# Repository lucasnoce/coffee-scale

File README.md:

# coffee-scale
Weight measuring device, targeted for coffee making

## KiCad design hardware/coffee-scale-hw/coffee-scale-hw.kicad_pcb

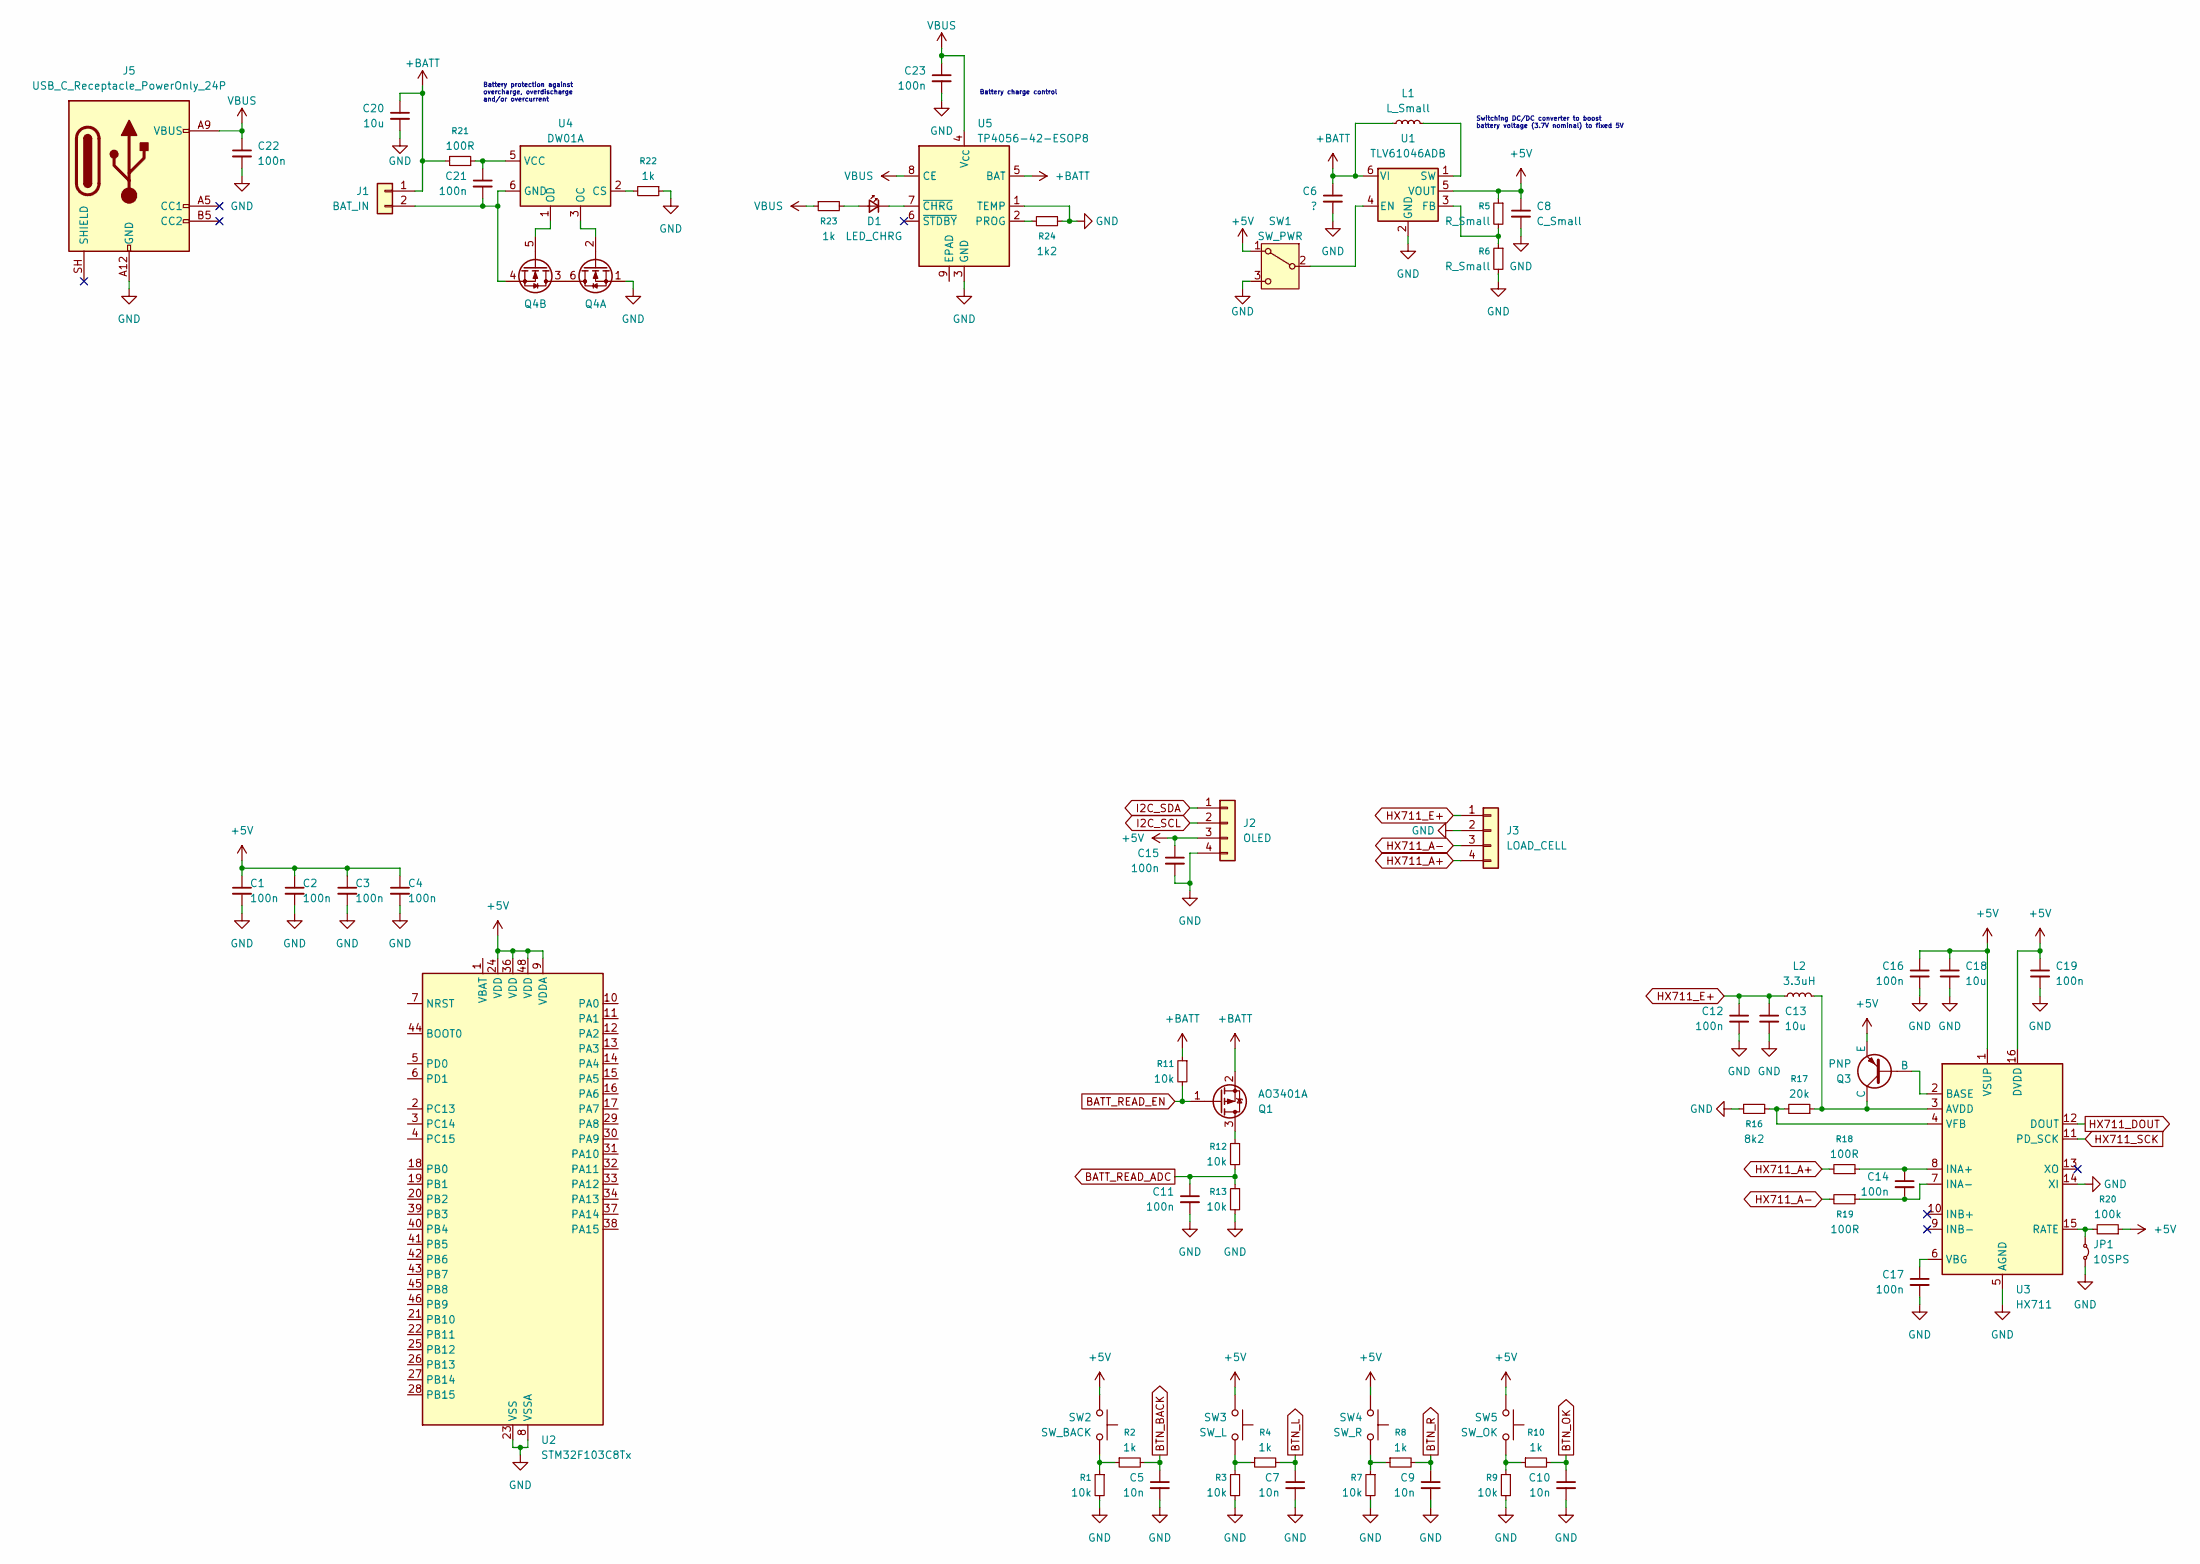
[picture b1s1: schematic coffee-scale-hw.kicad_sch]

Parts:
C1, C2, C3, C4, C11, C12, C14, C15, C16, C17, C19, C21, C22, C23: 100n; C_0805_2012Metric
C5, C7, C9, C10: 10n; C_0805_2012Metric
C6: ?; C_0805_2012Metric
C8: C_Small; C_0805_2012Metric
C13, C18, C20: 10u; C_0805_2012Metric
D1: LED_CHRG; LED_0805_2012Metric
J1: BAT_IN; Terminal_Pad_01x02-3x5mm
J2: OLED; Terminal_Pad_01x04-2x3mm
J3: LOAD_CELL; Terminal_Pad_01x04-2x3mm
J5: USB_C_Receptacle_PowerOnly_24P; USB_C_Receptacle_GCT_USB4125-xx-x_6P_TopMnt_Horizontal
JP1: 10SPS; SolderJumper-2_P1.3mm_Bridged_RoundedPad1.0x1.5mm
L1: L_Small; L_6.3x6.3_H3
L2: 3.3uH; L_0805_2012Metric
Q1: AO3401A; SOT-23
Q3: PNP; SOT-23
Q4: Q_Dual_NMOS_S1G1D2S2G2D1; SOT-363_SC-70-6
R1, R3, R7, R9, R11, R12, R13: 10k; R_0805_2012Metric
R2, R4, R8, R10, R22, R23: 1k; R_0805_2012Metric
R5, R6: R_Small; R_0805_2012Metric
R16: 8k2; R_0805_2012Metric
R17: 20k; R_0805_2012Metric
R18, R19, R21: 100R; R_0805_2012Metric
R20: 100k; R_0805_2012Metric
R24: 1k2; R_0805_2012Metric
SW1: SW_PWR; Sliding_Switch_MK-12C02-G020
SW2: SW_BACK; SW_TS-1187A-B-A-B
SW3: SW_L; SW_TS-1187A-B-A-B
SW4: SW_R; SW_TS-1187A-B-A-B
SW5: SW_OK; SW_TS-1187A-B-A-B
U1: TLV61046ADB; SOT-23-6
U2: STM32F103C8Tx; LQFP-48_7x7mm_P0.5mm
U3: HX711; SOIC-16_3.9x9.9mm_P1.27mm
U4: DW01A; SOT-23-6
U5: TP4056-42-ESOP8; SOIC-8-1EP_3.9x4.9mm_P1.27mm_EP2.41x3.3mm_ThermalVias

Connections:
+5V: C1.1, C2.1, C3.1, C4.1, C8.1, C15.1, C16.1, C18.1, C19.1, J2.3, Q3.3 (E), R5.1, R20.1, SW1.1 (A), SW2.2, SW3.2, SW4.2, SW5.2, U1.5 (VOUT), U2.9 (VDDA), U2.24 (VDD), U2.36 (VDD), U2.48 (VDD), U3.1 (VSUP), U3.16 (DVDD)
+BATT: C6.1, C20.1, J1.1, L1.1, Q1.2 (S), R11.1, R21.2, U1.6 (VI), U5.5 (BAT)
BATT_READ_ADC: C11.1, R12.2, R13.1
BATT_READ_EN: Q1.1 (G), R11.2
BTN_BACK: C5.1, R2.2
BTN_L: C7.1, R4.2
BTN_OK: C10.1, R10.2
BTN_R: C9.1, R8.2
GND: C1.2, C2.2, C3.2, C4.2, C5.2, C6.2, C7.2, C8.2, C9.2, C10.2, C11.2, C12.2, C13.2, C15.2, C16.2, C17.2, C18.2, C19.2, C20.2, C22.2, C23.2, J2.4, J3.2, J5.A1 (GND), J5.A12 (GND), J5.B1 (GND), J5.B12 (GND), JP1.2 (B), Q4.1 (S), R1.2, R3.2, R6.2, R7.2, R9.2, R13.2, R16.2, R22.1, R24.1, SW1.3 (C), U1.2 (GND), U2.8 (VSSA), U2.23 (VSS), U2.35 (VSS), U2.47 (VSS), U3.5 (AGND), U3.14 (XI), U5.1 (TEMP), U5.3 (GND)
HX711_A+: J3.4, R18.2
HX711_A-: J3.3, R19.2
HX711_DOUT: U3.12 (DOUT)
HX711_E+: C12.1, C13.1, J3.1, L2.1
HX711_SCK: U3.11 (PD_SCK)
I2C_SCL: J2.2
I2C_SDA: J2.1
unnamed: D1.2 (A), R23.2
unnamed: D1.1 (K), U5.7 (~CHRG)
unnamed: C21.2, J1.2, Q4.4 (S), U4.6 (GND)
unnamed: JP1.1 (A), R20.2, U3.15 (RATE)
unnamed: Q1.3 (D), R12.1
unnamed: Q3.2 (B), U3.2 (BASE)
unnamed: L2.2, Q3.1 (C), R17.1, U3.3 (AVDD)
unnamed: Q4.3 (D), Q4.6 (D)
unnamed: Q4.2 (G), U4.3 (OC)
unnamed: Q4.5 (G), U4.1 (OD)
unnamed: R1.1, R2.1, SW2.1
unnamed: R3.1, R4.1, SW3.1
unnamed: R7.1, R8.1, SW4.1
unnamed: R9.1, R10.1, SW5.1
unnamed: SW1.2 (B), U1.4 (EN)
unnamed: R5.2, R6.1, U1.3 (FB)
unnamed: L1.2, U1.1 (SW)
unnamed: C14.1, R18.1, U3.8 (INA+)
unnamed: C14.2, R19.1, U3.7 (INA-)
unnamed: C17.1, U3.6 (VBG)
unnamed: R16.1, R17.2, U3.4 (VFB)
unnamed: R22.2, U4.2 (CS)
unnamed: C21.1, R21.1, U4.5 (VCC)
unnamed: R24.2, U5.2 (PROG)
VBUS: C22.1, C23.1, J5.A4 (VBUS), J5.A9 (VBUS), J5.B4 (VBUS), J5.B9 (VBUS), R23.1, U5.4 (V_{CC}), U5.8 (CE)

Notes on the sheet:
Battery protection against overcharge, overdischarge and/or overcurrent
Battery charge control
Switching DC/DC converter to boost battery voltage (3.7V nominal) to fixed 5V

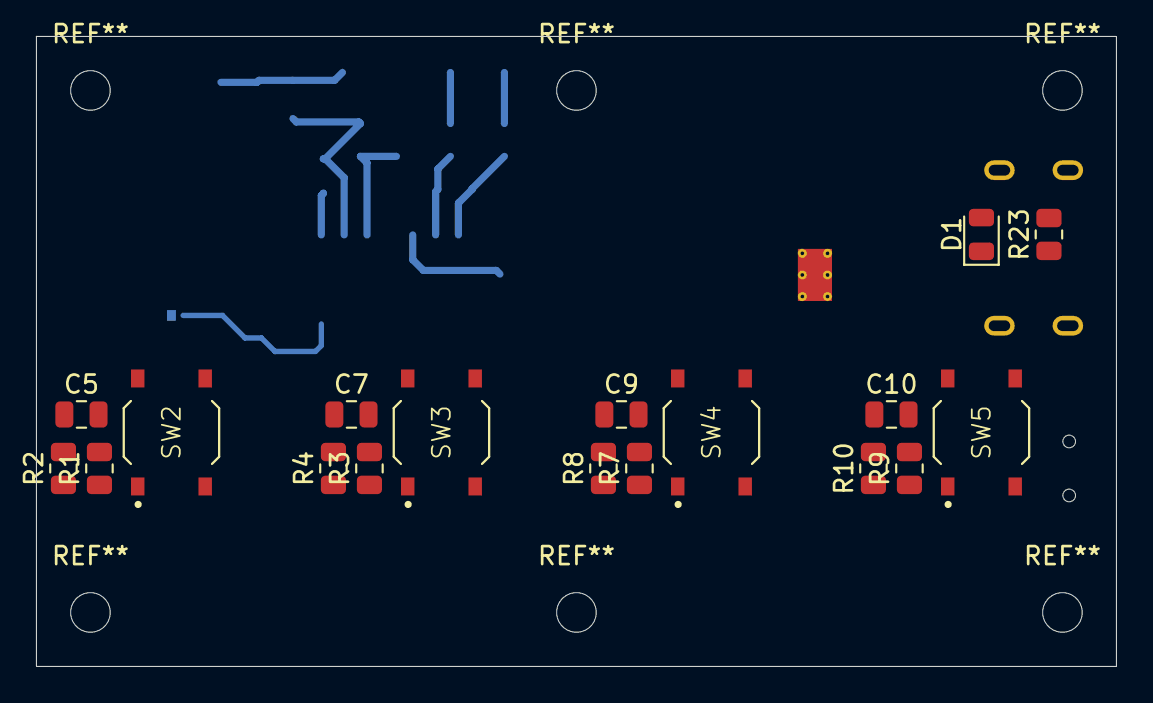
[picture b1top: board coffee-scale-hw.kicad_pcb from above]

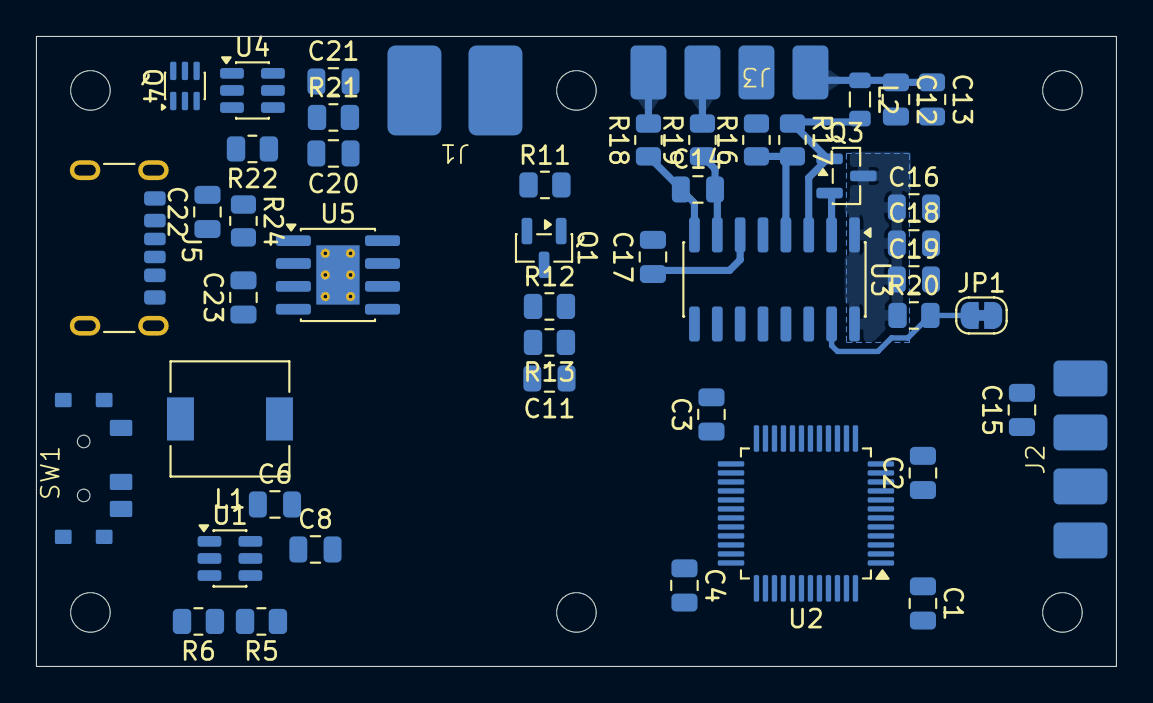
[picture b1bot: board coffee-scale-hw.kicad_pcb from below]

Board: 2 copper layers, 60.0 x 35.0 mm, 66 parts (48 on the bottom side), 37 nets.

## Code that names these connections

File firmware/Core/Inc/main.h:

/* USER CODE BEGIN Header */
/**
  ******************************************************************************
  * @file           : main.h
  * @brief          : Header for main.c file.
  *                   This file contains the common defines of the application.
  ******************************************************************************
  * @attention
  *
  * Copyright (c) 2026 STMicroelectronics.
  * All rights reserved.
  *
  * This software is licensed under terms that can be found in the LICENSE file
  * in the root directory of this software component.
  * If no LICENSE file comes with this software, it is provided AS-IS.
  *
  ******************************************************************************
  */
/* USER CODE END Header */

/* Define to prevent recursive inclusion -------------------------------------*/
#ifndef __MAIN_H
#define __MAIN_H

#ifdef __cplusplus
extern "C" {
#endif

/* Includes ------------------------------------------------------------------*/
#include "stm32f4xx_hal.h"

/* Private includes ----------------------------------------------------------*/
/* USER CODE BEGIN Includes */

/* USER CODE END Includes */

/* Exported types ------------------------------------------------------------*/
/* USER CODE BEGIN ET */

/* USER CODE END ET */

/* Exported constants --------------------------------------------------------*/
/* USER CODE BEGIN EC */

/* USER CODE END EC */

/* Exported macro ------------------------------------------------------------*/
/* USER CODE BEGIN EM */

/* USER CODE END EM */

/* Exported functions prototypes ---------------------------------------------*/
void Error_Handler(void);

/* USER CODE BEGIN EFP */

/* USER CODE END EFP */

/* Private defines -----------------------------------------------------------*/
#define BTN_BACK_Pin GPIO_PIN_3
#define BTN_BACK_GPIO_Port GPIOA
#define BTN_BACK_EXTI_IRQn EXTI3_IRQn
#define BTN_L_Pin GPIO_PIN_4
#define BTN_L_GPIO_Port GPIOA
#define BTN_L_EXTI_IRQn EXTI4_IRQn
#define BTN_R_Pin GPIO_PIN_5
#define BTN_R_GPIO_Port GPIOA
#define BTN_R_EXTI_IRQn EXTI9_5_IRQn
#define BTN_OK_Pin GPIO_PIN_6
#define BTN_OK_GPIO_Port GPIOA
#define BTN_OK_EXTI_IRQn EXTI9_5_IRQn
#define HX711_DOUT_LoopBack_Pin GPIO_PIN_8
#define HX711_DOUT_LoopBack_GPIO_Port GPIOA
#define HX711_SCK_LoopBack_Pin GPIO_PIN_9
#define HX711_SCK_LoopBack_GPIO_Port GPIOA
#define HX711_SCK_LoopBack_EXTI_IRQn EXTI9_5_IRQn
#define HX711_SCK_Pin GPIO_PIN_10
#define HX711_SCK_GPIO_Port GPIOA
#define HX711_DOUT_Pin GPIO_PIN_11
#define HX711_DOUT_GPIO_Port GPIOA
#define HX711_DOUT_EXTI_IRQn EXTI15_10_IRQn

/* USER CODE BEGIN Private defines */

/* USER CODE END Private defines */

#ifdef __cplusplus
}
#endif

#endif /* __MAIN_H */

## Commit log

2026-06-10 Created STM32CubeIDE project and git folder structure
2026-06-10 Implemented display timer, flow and mass
2026-06-11 Added support for HX711
2026-06-12 Added buttons and events
2026-06-12 Reorganized button structure
2026-06-17 Debugging
2026-06-17 Starting HW desing
2026-06-17 Working on HW design
2026-06-19 Simplified hx711 test functionality and fixed some bugs
2026-06-19 Working on hx711 test improvements
2026-06-19 Improved hx711 init
2026-06-19 Added LiPo battery USB-C charger
